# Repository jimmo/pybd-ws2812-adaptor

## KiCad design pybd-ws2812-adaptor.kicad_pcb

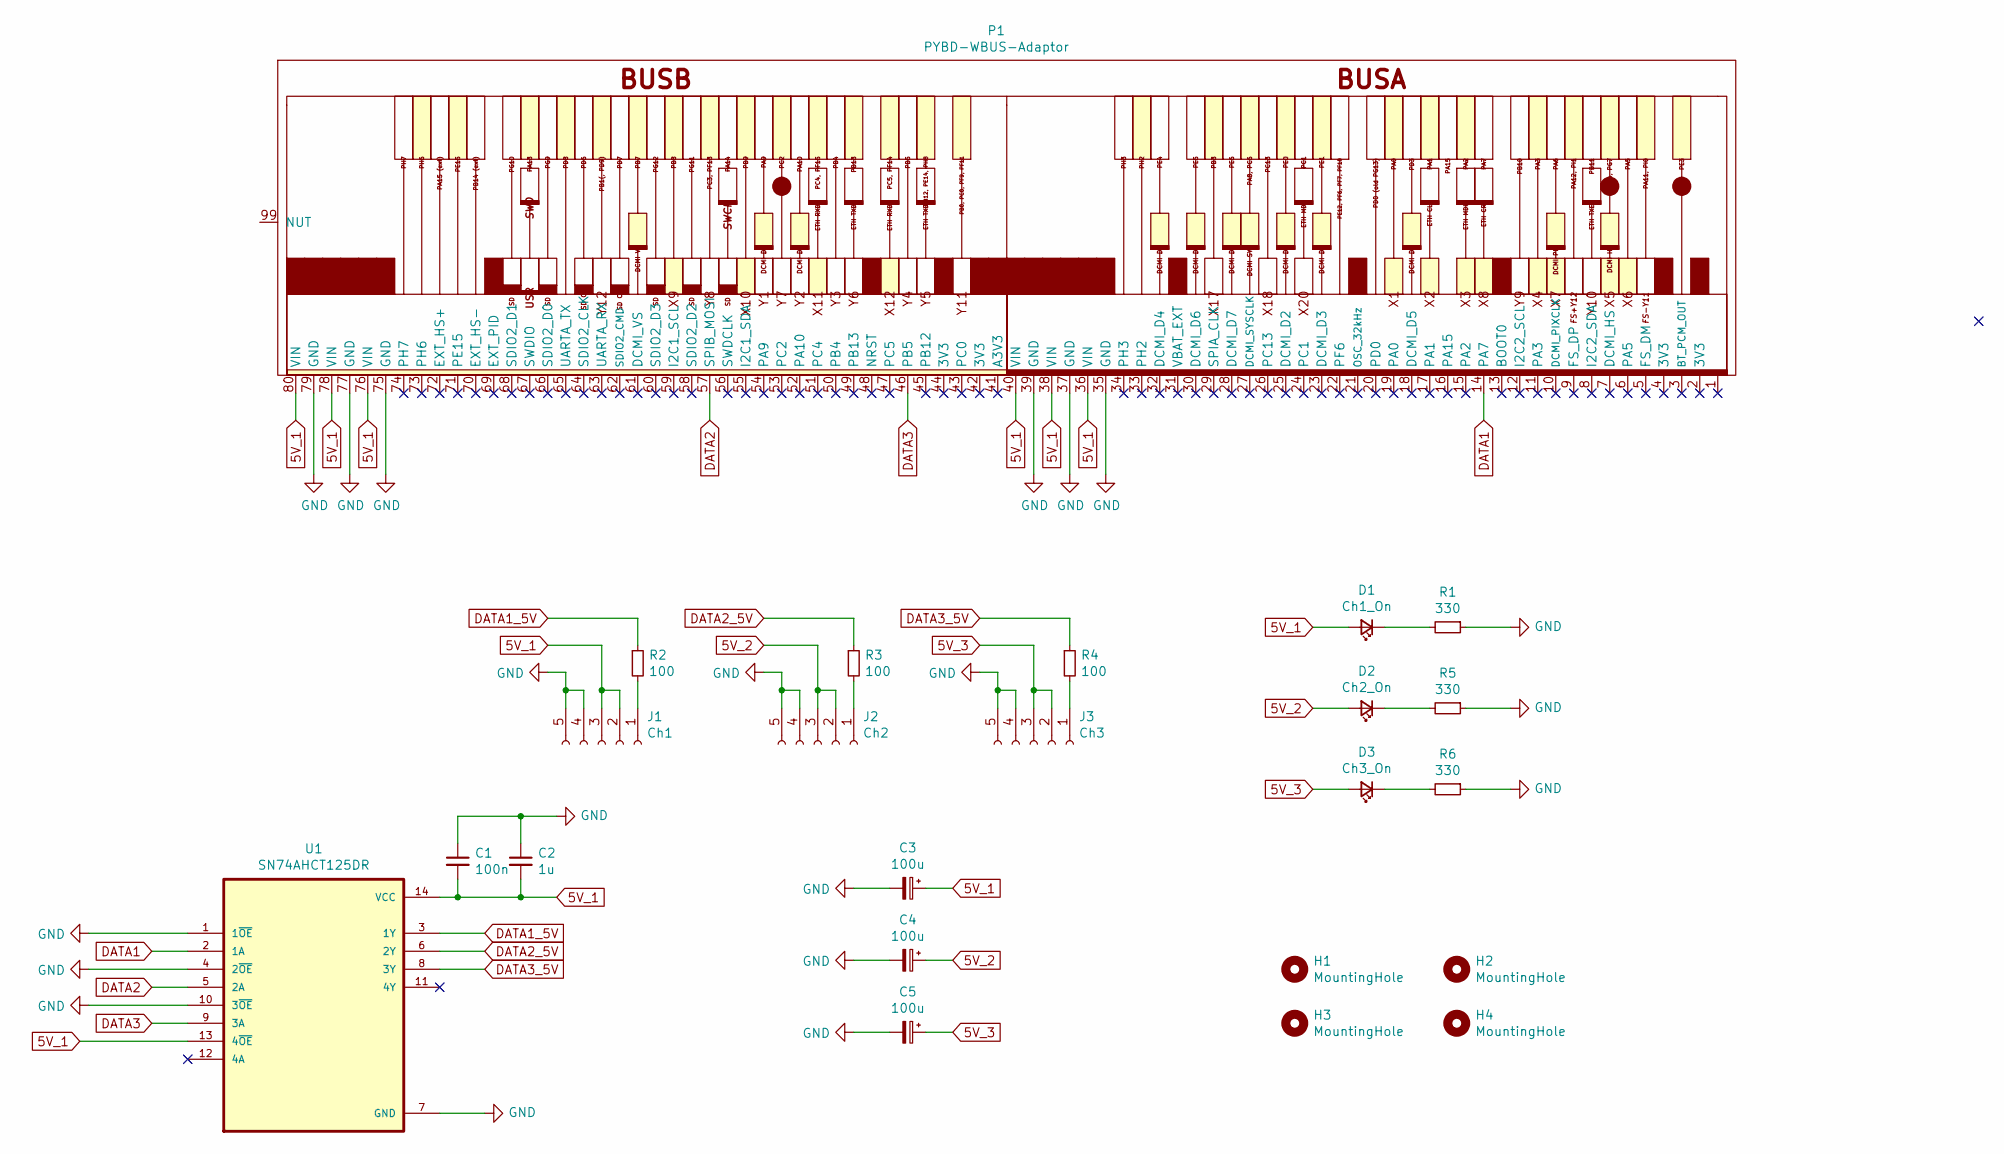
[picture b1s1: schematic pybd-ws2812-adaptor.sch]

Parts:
C1: 100n; C_0603_1608Metric_Pad1.08x0.95mm_HandSolder
C2: 1u; C_0603_1608Metric_Pad1.08x0.95mm_HandSolder
C3, C4, C5: 100u; CP_Radial_D8.0mm_P2.50mm
D1: Ch1_On; LED_0603_1608Metric_Pad1.05x0.95mm_HandSolder
D2: Ch2_On; LED_0603_1608Metric_Pad1.05x0.95mm_HandSolder
D3: Ch3_On; LED_0603_1608Metric_Pad1.05x0.95mm_HandSolder
H1, H2, H3, H4: MountingHole; MountingHole_3.2mm_M3
J1: Ch1; TerminalBlock_MetzConnect_Type011_RT05505HBWC_1x05_P5.00mm_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
J2: Ch2; TerminalBlock_MetzConnect_Type011_RT05505HBWC_1x05_P5.00mm_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
J3: Ch3; TerminalBlock_MetzConnect_Type011_RT05505HBWC_1x05_P5.00mm_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
P1: PYBD-WBUS-Adaptor; PYBD_WBUS_Adaptor
R1, R5, R6: 330; R_0603_1608Metric_Pad0.98x0.95mm_HandSolder
R2, R3, R4: 100; R_0603_1608Metric_Pad0.98x0.95mm_HandSolder
U1: SN74AHCT125DR; SOIC127P600X175-14N

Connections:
5V_1: C1.2, C2.2, C3.1, D1.2 (A), J1.2, J1.3, P1.36 (VIN), P1.38 (VIN), P1.40 (VIN), P1.76 (VIN), P1.78 (VIN), P1.80 (VIN), U1.13 (4~OE), U1.14 (VCC)
5V_2: C4.1, D2.2 (A), J2.2, J2.3
5V_3: C5.1, D3.2 (A), J3.2, J3.3
DATA1: P1.14 (PA7), U1.2 (1A)
DATA1_5V: R2.1, U1.3 (1Y)
DATA2: P1.57 (SPIB_MOSI), U1.5 (2A)
DATA2_5V: R3.1, U1.6 (2Y)
DATA3: P1.46 (PB5), U1.9 (3A)
DATA3_5V: R4.1, U1.8 (3Y)
GND: C1.1, C2.1, C3.2, C4.2, C5.2, J1.4, J1.5, J2.4, J2.5, J3.4, J3.5, P1.35 (GND), P1.37 (GND), P1.39 (GND), P1.75 (GND), P1.77 (GND), P1.79 (GND), R1.1, R5.1, R6.1, U1.1 (1~OE), U1.4 (2~OE), U1.7 (GND), U1.10 (3~OE)
unnamed: D1.1 (K), R1.2
unnamed: D2.1 (K), R5.2
unnamed: D3.1 (K), R6.2
unnamed: J1.1, R2.2
unnamed: J2.1, R3.2
unnamed: J3.1, R4.2

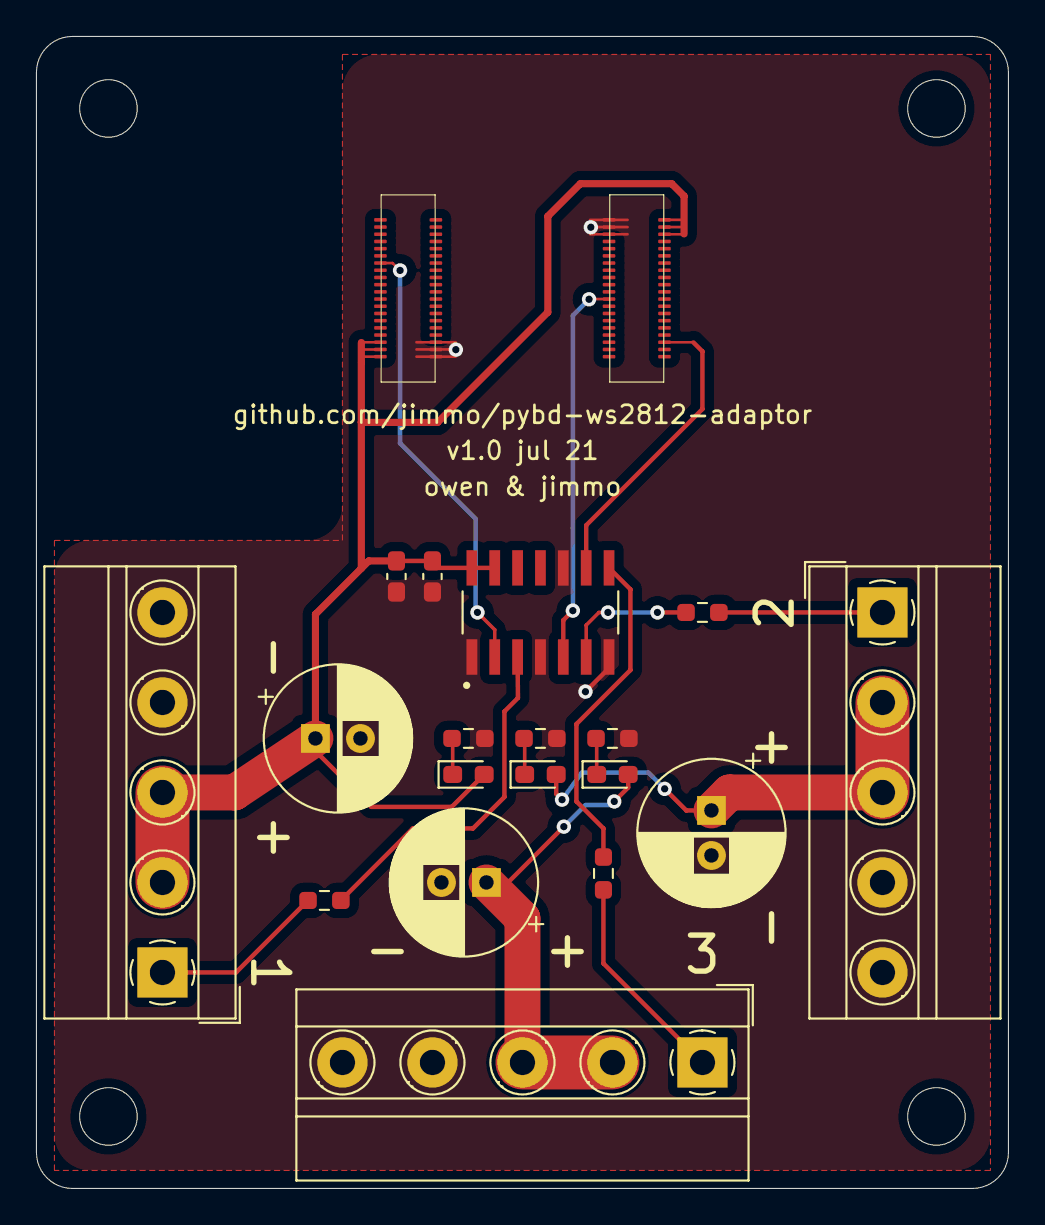
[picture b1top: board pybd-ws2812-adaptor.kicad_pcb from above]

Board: 2 copper layers, 54.0 x 64.0 mm, 23 parts (0 on the bottom side), 16 nets.

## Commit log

2021-07-20 Initial schematic and draft PCB.
2021-07-20 Board v1.0
2021-07-20 Rename to pybd-ws2812-adaptor
2021-07-21 Remove ground plane around antenna.
